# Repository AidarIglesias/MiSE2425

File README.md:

# MiSE2425
This repository is intended to work as a tracking tool for the project in the subject of Microcontollers and Embedded Systems at the University of Barcelona.

The project comprises of four main stages, listed as follows:

1. Resource Planning
2. Hardware Design
    1. Schematic Drawing
        1. Component distribution
        2. Wiring
        3. Labeling
        4. Annotating
        5. ERC Check
    2. PCB Layout
        1. Set design rules
        2. Import components from Schematic
        3. Placement
            1. Microcontroller
            2. RF sensitive components
            3. Power supply
            4. The rest
        4. Routing
            1. RF & High speed lines
            2. Differential pair lines
            3. Power lines
            4. The rest
        5. Copper pouring
    3. PCB Assembly & Soldering
3. Software Design
    1. Creating the workspace
    2. Importing libraries
    3. Creating sub-files
    4. Coding
    5. Building
    6. Test runs
    7. Optimizing the code
    8. Reparsing
    9. Decorating
4. Project Presentation

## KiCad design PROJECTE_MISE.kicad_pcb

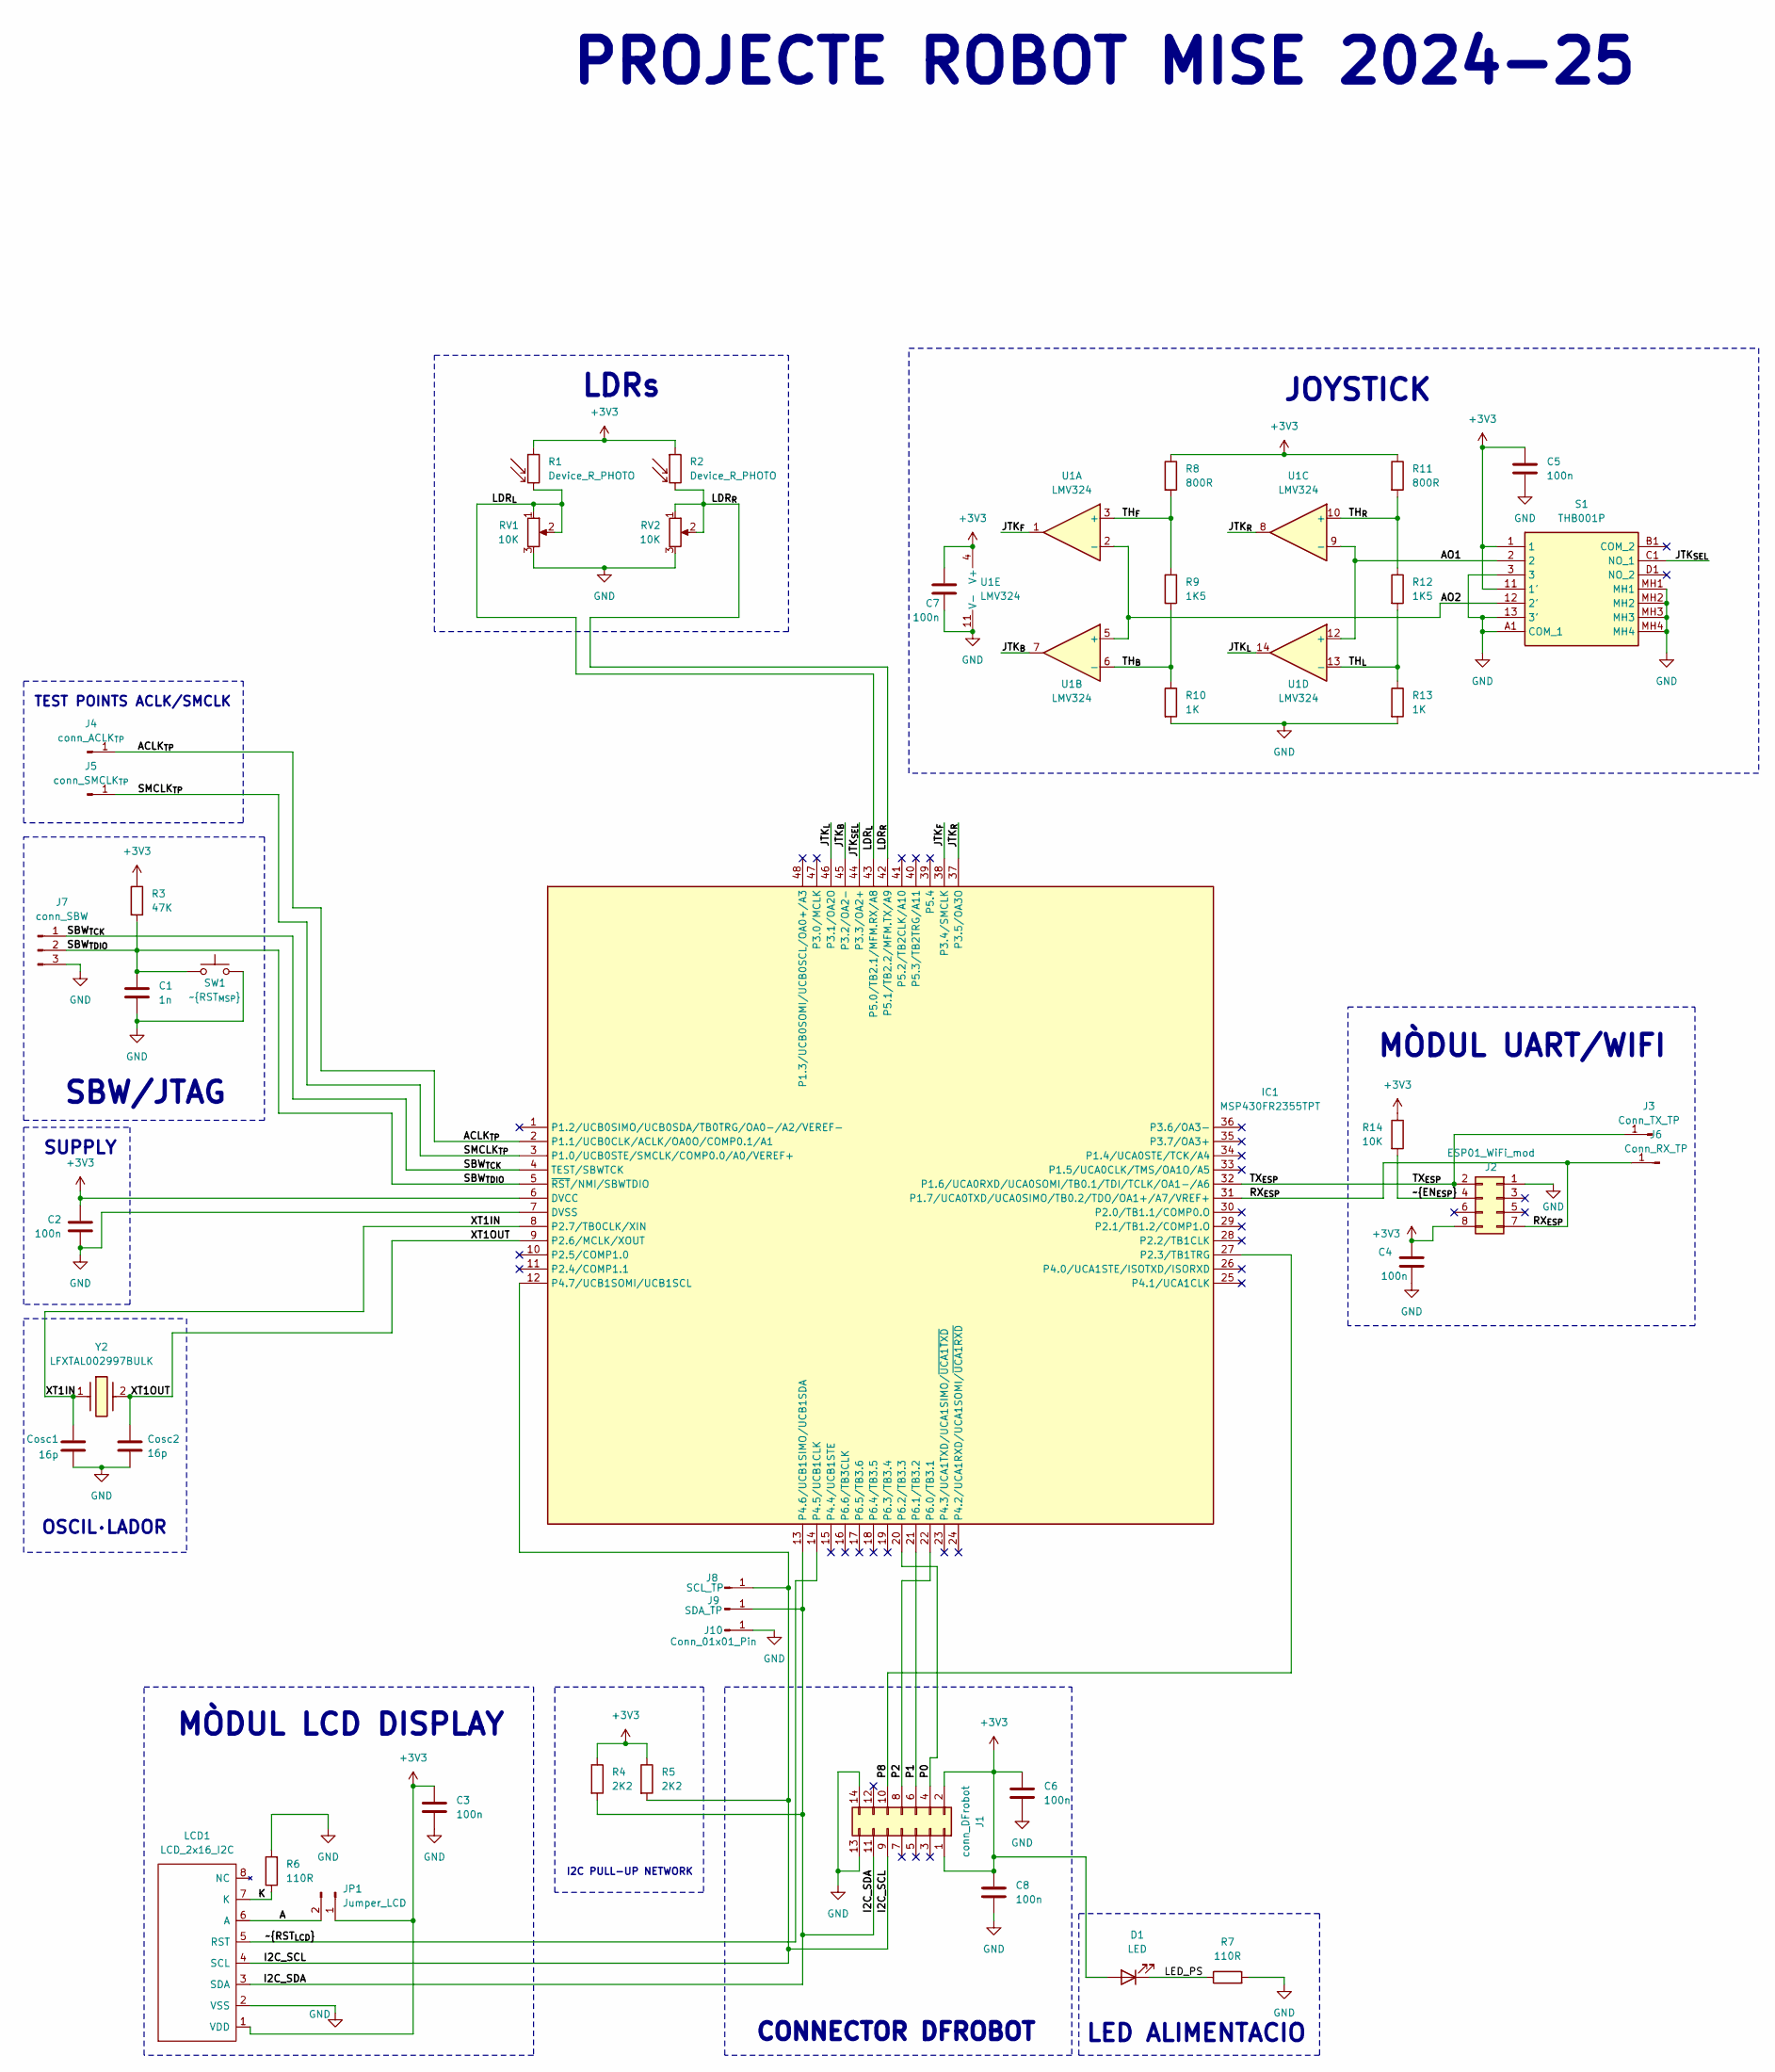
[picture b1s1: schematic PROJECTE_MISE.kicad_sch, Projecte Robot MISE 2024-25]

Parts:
C1: 1n; C_0805_2012Metric
C2, C3, C4, C5, C6, C7, C8: 100n; C_0805_2012Metric
Cosc1, Cosc2: 16p; C_0805_2012Metric
D1: LED; LED_0805_2012Metric
IC1: MSP430FR2355TPT; QFP50P900X900X160-48N; Manufacturer_Part_Number MSP430FR2355TPT; Mouser Part Number 595-MSP430FR2355TPT
J1: conn_DFrobot
J2: ESP01_WiFi_mod; PinSocket_2x04_P2.54mm_Vertical
J3: Conn_TX_TP; PinHeader_1x01_P2.00mm_Vertical
J4: conn_ACLK_{TP}; PinHeader_1x01_P2.00mm_Vertical
J5: conn_SMCLK_{TP}; PinHeader_1x01_P2.00mm_Vertical
J6: Conn_RX_TP; PinHeader_1x01_P2.00mm_Vertical
J7: conn_SBW; PinHeader_1x03_P2.54mm_Vertical
J8: SCL_TP; PinHeader_1x01_P2.00mm_Vertical
J9: SDA_TP; PinHeader_1x01_P2.00mm_Vertical
J10: Conn_01x01_Pin; PinHeader_1x01_P2.00mm_Vertical
JP1: Jumper_LCD; PinHeader_2x01_P2.00mm_Vertical
LCD1: LCD_2x16_I2C; LCD_2x16_I2C(Midas)
R1, R2: Device_R_PHOTO; LDR
R3: 47K; R_0805_2012Metric
R4, R5: 2K2; R_0805_2012Metric
R6, R7: 110R; R_0805_2012Metric
R8, R11: 800R; R_0805_2012Metric
R9, R12: 1K5; R_0805_2012Metric
R10, R13: 1K; R_0805_2012Metric
R14: 10K; R_0805_2012Metric
RV1, RV2: 10K; Trimmer_MiSE
S1: THB001P; Manufacturer_Part_Number THB001P; Mouser Part Number 611-THB001P
SW1: ~{RST_{MSP}}; SW_PUSH_6mm
U1: LMV324; SOIC-14_3.9x8.7mm_P1.27mm
Y2: LFXTAL002997BULK; LFXTAL002997Bulk_modificat; Mouser Part Number 449-LFXTAL002997BULK

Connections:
+3V3: C2.1, C3.1, C4.1, C5.1, C6.1, C7.1, C8.1, D1.2 (A), IC1.6 (DVCC), J1.1, J1.2, J2.8, JP1.1, LCD1.1 (VDD), R1.1, R2.1, R3.1, R4.1, R5.1, R8.1, R11.1, R14.1, S1.1, S1.11 (1'), U1.4 (V+)
/A: JP1.2, LCD1.6 (A)
/ACLK_{TP}: IC1.2 (P1.1/UCB0CLK/ACLK/OA0O/COMP0.1/A1), J4.1
/AO1: S1.2, U1.9 (-), U1.12 (+)
/AO2: S1.12 (2'), U1.2 (-), U1.5 (+)
/I2C_SCL: IC1.12 (P4.7/UCB1SOMI/UCB1SCL), J1.9, J8.1, LCD1.4 (SCL), R5.2
/I2C_SDA: IC1.13 (P4.6/UCB1SIMO/UCB1SDA), J1.11, J9.1, LCD1.3 (SDA), R4.2
/JTK_{B}: IC1.45 (P3.2/OA2-), U1.7
/JTK_{F}: IC1.38 (P3.4/SMCLK), U1.1
/JTK_{L}: IC1.46 (P3.1/OA2O), U1.14
/JTK_{R}: IC1.37 (P3.5/OA3O), U1.8
/JTK_{SEL}: IC1.44 (P3.3/OA2+), S1.C1 (NO_1)
/K: LCD1.7 (K), R6.1
/LDR_{L}: IC1.43 (P5.0/TB2.1/MFM.RX/A8), R1.2, RV1.1, RV1.2
/LDR_{R}: IC1.42 (P5.1/TB2.2/MFM.TX/A9), R2.2, RV2.1, RV2.2
/LED_PS: D1.1 (K), R7.1
/P0: IC1.20 (P6.2/TB3.3), J1.4
/P1: IC1.21 (P6.1/TB3.2), J1.6
/P2: IC1.22 (P6.0/TB3.1), J1.8
/P8: IC1.27 (P2.3/TB1TRG), J1.10
/RX_{ESP}: IC1.31 (P1.7/UCA0TXD/UCA0SIMO/TB0.2/TDO/OA1+/A7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), J2.7, J6.1
/SBW_{TCK}: IC1.4 (TEST/SBWTCK), J7.1
/SBW_{TDIO}: C1.1, IC1.5 (~RST/NMI/SBWTDIO), J7.2, R3.2, SW1.1
/SMCLK_{TP}: IC1.3 (P1.0/UCB0STE/SMCLK/COMP0.0/A0/VEREF+), J5.1
/TH_{B}: R9.2, R10.1, U1.6 (-)
/TH_{F}: R8.2, R9.1, U1.3 (+)
/TH_{L}: R12.2, R13.1, U1.13 (-)
/TH_{R}: R11.2, R12.1, U1.10 (+)
/TX_{ESP}: IC1.32 (P1.6/UCA0RXD/UCA0SOMI/TB0.1/TDI/TCLK/OA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), J2.2, J3.1
/XT1IN: Cosc1.1, IC1.8 (P2.7/TB0CLK/XIN), Y2.1
/XT1OUT: Cosc2.1, IC1.9 (P2.6/MCLK/XOUT), Y2.2
/~EN_{ESP}: J2.4, R14.2
/~RST_{LCD}: IC1.14 (P4.5/UCB1CLK), LCD1.5 (RST)
GND: C1.2, C2.2, C3.2, C4.2, C5.2, C6.2, C7.2, C8.2, Cosc1.2, Cosc2.2, IC1.7 (DVSS), J1.13, J1.14, J2.1, J7.3, J10.1, LCD1.2 (VSS), R6.2, R7.2, R10.2, R13.2, RV1.3, RV2.3, S1.3, S1.13 (3'), S1.A1 (COM_1), S1.MH1, S1.MH2, S1.MH3, S1.MH4, SW1.2, U1.11 (V-)

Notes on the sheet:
OSCIL·LADOR
TEST POINTS ACLK/SMCLK
PROJECTE ROBOT MISE 2024-25
MÒDUL UART/WIFI
SUPPLY
I2C PULL-UP NETWORK
CONNECTOR DFROBOT
MÒDUL LCD DISPLAY
SBW/JTAG
LED ALIMENTACIO
LDRs
JOYSTICK

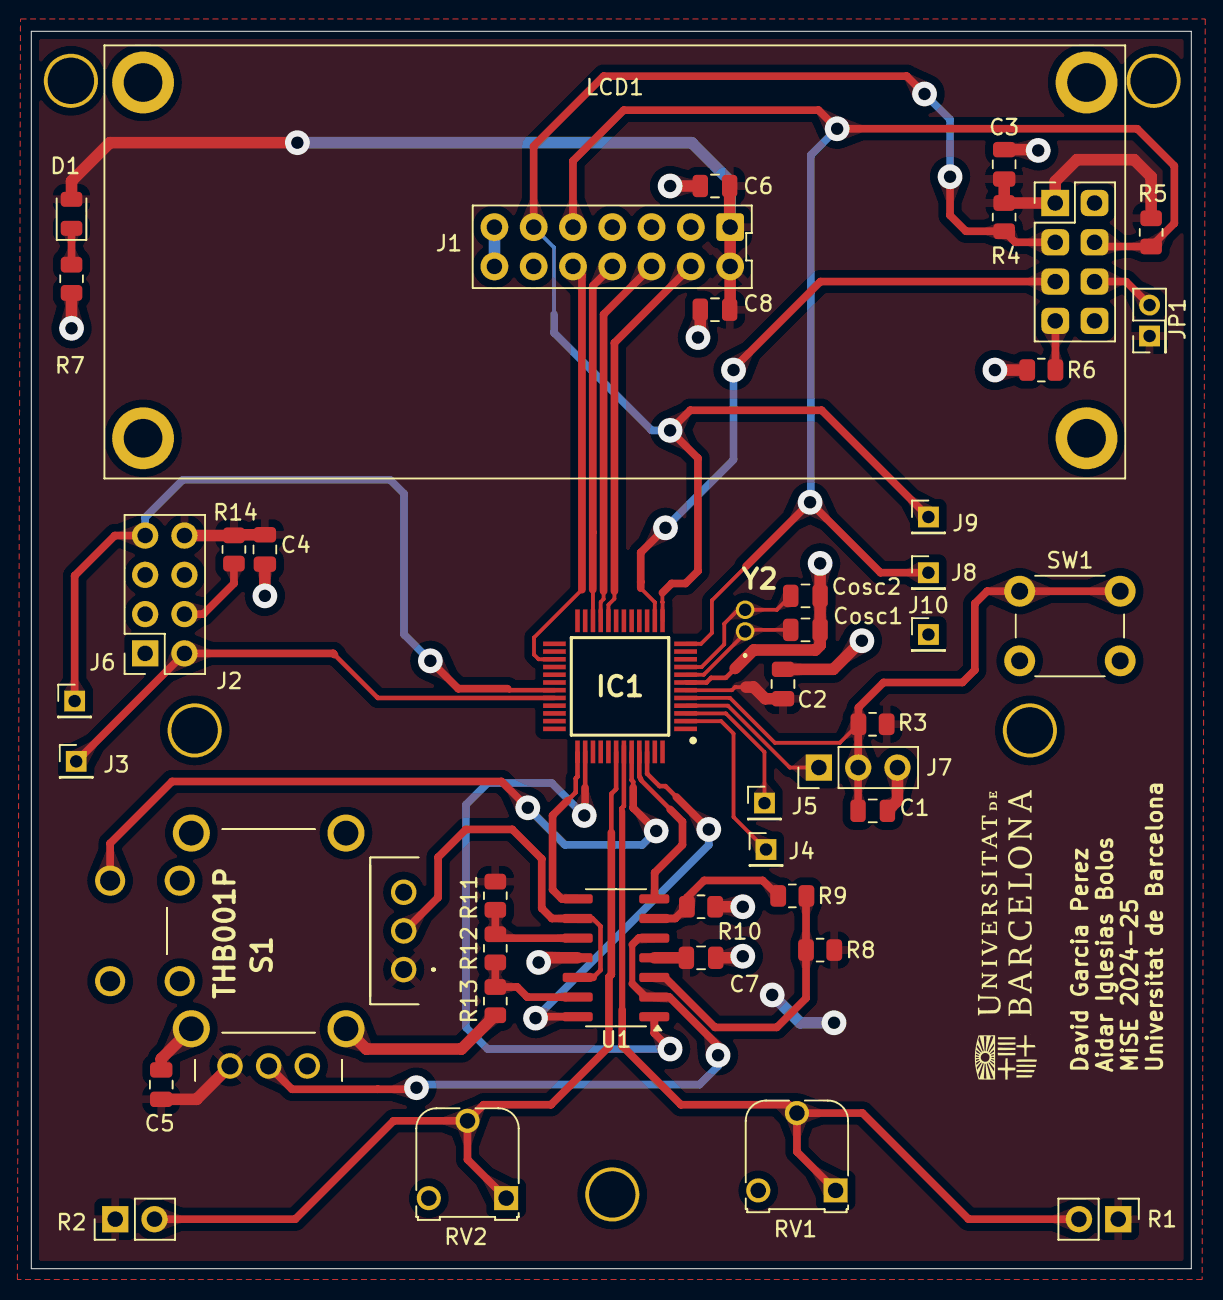
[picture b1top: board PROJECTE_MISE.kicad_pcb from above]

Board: 2 copper layers, 75.0 x 80.0 mm, 44 parts (0 on the bottom side), 34 nets.

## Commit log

2025-02-27 added design files and gitignore
2025-02-27 added GPLv3 license file
2025-02-27 rotate conn_DFRobot image
2025-02-27 Revert "rotate conn_DFRobot image"
    This reverts commit 6e819256481b9d06e6faf2437fc47867e73514bb.
2025-02-27 LDR image
2025-02-27 modul wifi girat
2025-02-28 updated wifi & crystal
2025-02-28 huellas
2025-02-28 huellas_complet
2025-02-28 first layout placement
2025-02-28 layout better
2025-03-04 placement i canvi esqu.
2025-03-04 acabat
2025-03-07 layout conn_robot
2025-03-08 layout with LDRs and better conn
2025-03-08 layout ESP module and comparators
2025-03-08 algun canvi apart
2025-03-09 layout new placement and nee changes
2025-03-09 update layout - routing
2025-03-10 layout finished but it has to be checked
2025-03-10 modificacions layout
2025-03-10 layout 0 errors 0 warnings
2025-03-11 layout finished 0 errors, 0 warnings and solved problems
2025-03-11 final layout + gerbers
2025-03-12 fixes layout + pending VCC LED, C ESP & redraw gerbers
2025-03-12 layout finished
2025-03-14 update R value LED_PS + update gerber files
2025-03-14 zip file created
2025-03-17 gerbers update and final version
2025-04-23 added SW files for first time
